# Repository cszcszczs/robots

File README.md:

# Robots (Velocista y Sumo)

##  Esquema de montaje

### *fuente esquemas: https://www.luisllamas.es/arduino-motor-dc-tb6612fng/*
### *fuente codigo base sumo: https://www.youtube.com/watch?v=NjcQ3KwS5uU&t=53s*

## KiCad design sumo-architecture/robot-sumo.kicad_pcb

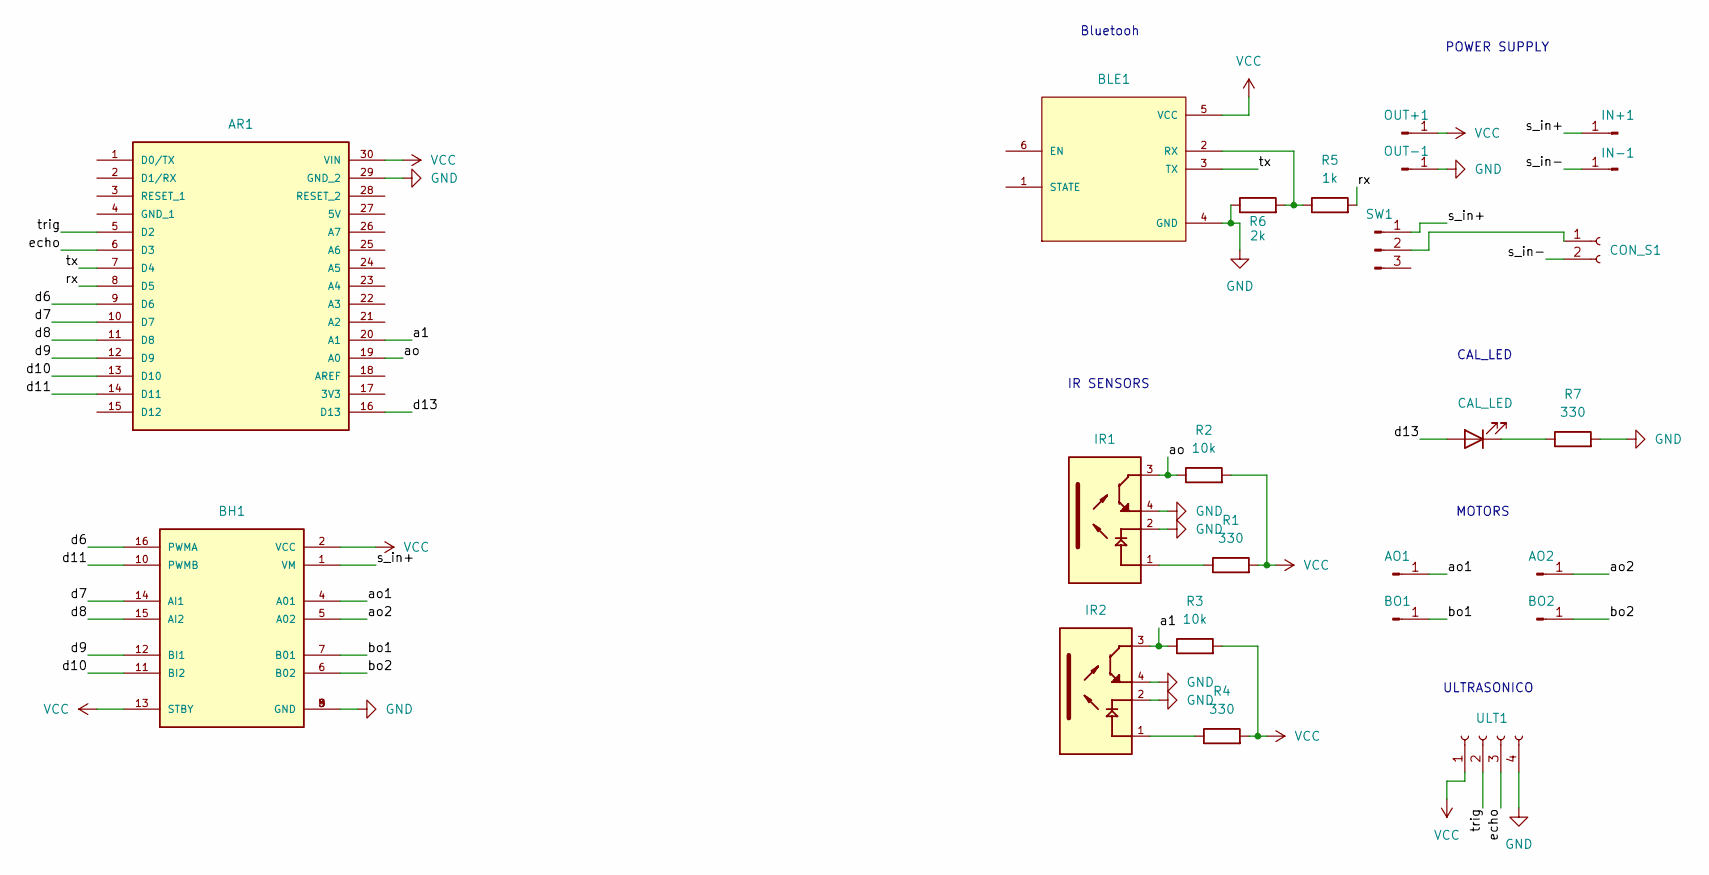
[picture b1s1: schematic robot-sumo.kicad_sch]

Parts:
AO1, AO2: Conn_01x01_Pin; PinHeader_1x01_P1.00mm_Vertical
AR1: A000005; MODULE_A000005; PARTREV 23/03/2020
BH1: ROB-14450; MODULE_ROB-14450; PARTREV 11-13-17
BLE1: ZC142200; MODULE_ZC142200; PARTREV N/A
BO1, BO2: Conn_01x01_Pin; PinHeader_1x01_P1.00mm_Vertical
CAL_LED1: CAL_LED; LED_D5.0mm
CON_S1: Conn_01x02_Socket; AMASS_XT60-M_1x02_P7.20mm_Vertical
IN+1: Conn_01x01_Pin; PinHeader_1x01_P1.00mm_Vertical
IN-1: Conn_01x01_Pin; PinHeader_1x01_P1.00mm_Vertical
IR1, IR2: QRE1113; DIP400W50P180L360H200Q4; PARTREV 5
OUT+1: Conn_01x01_Pin; PinHeader_1x01_P1.00mm_Vertical
OUT-1: Conn_01x01_Pin; PinHeader_1x01_P1.00mm_Vertical
R1, R4, R7: 330; R_Axial_DIN0204_L3.6mm_D1.6mm_P7.62mm_Horizontal
R2, R3: 10k; R_Axial_DIN0204_L3.6mm_D1.6mm_P7.62mm_Horizontal
R5: 1k; R_Axial_DIN0204_L3.6mm_D1.6mm_P7.62mm_Horizontal
R6: 2k; R_Axial_DIN0204_L3.6mm_D1.6mm_P7.62mm_Horizontal
SW1: Conn_01x03_Pin; PinHeader_1x03_P1.00mm_Vertical
ULT1: Conn_01x04_Socket; PinHeader_1x04_P2.00mm_Vertical

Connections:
/a1: AR1.20 (A1), IR2.3, R3.1
/ao: AR1.19 (A0), IR1.3, R2.1
/ao1: AO1.1, BH1.4 (A01)
/ao2: AO2.1, BH1.5 (A02)
/bo1: BH1.7 (B01), BO1.1
/bo2: BH1.6 (B02), BO2.1
/d6: AR1.9 (D6), BH1.16 (PWMA)
/d7: AR1.10 (D7), BH1.14 (AI1)
/d8: AR1.11 (D8), BH1.15 (AI2)
/d9: AR1.12 (D9), BH1.12 (BI1)
/d10: AR1.13 (D10), BH1.11 (BI2)
/d11: AR1.14 (D11), BH1.10 (PWMB)
/d13: AR1.16 (D13), CAL_LED1.2 (A)
/echo: AR1.6 (D3), ULT1.3
/rx: AR1.8 (D5), R5.2
/s_in+: BH1.1 (VM), IN+1.1, SW1.1
/s_in-: CON_S1.2, IN-1.1
/trig: AR1.5 (D2), ULT1.2
/tx: AR1.7 (D4), BLE1.3 (TX)
GND: AR1.29 (GND_2), BH1.3 (GND), BH1.8 (GND), BH1.9 (GND), BLE1.4 (GND), IR1.2, IR1.4, IR2.2, IR2.4, OUT-1.1, R6.1, R7.2, ULT1.4
unnamed: BLE1.2 (RX), R5.1, R6.2
unnamed: CAL_LED1.1 (K), R7.1
unnamed: CON_S1.1, SW1.2
unnamed: IR1.1, R1.1
unnamed: IR2.1, R4.1
VCC: AR1.30 (VIN), BH1.2 (VCC), BH1.13 (STBY), BLE1.5 (VCC), OUT+1.1, R1.2, R2.2, R3.2, R4.2, ULT1.1

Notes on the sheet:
POWER SUPPLY
ULTRASONICO
IR SENSORS
Bluetooh
CAL_LED
MOTORS

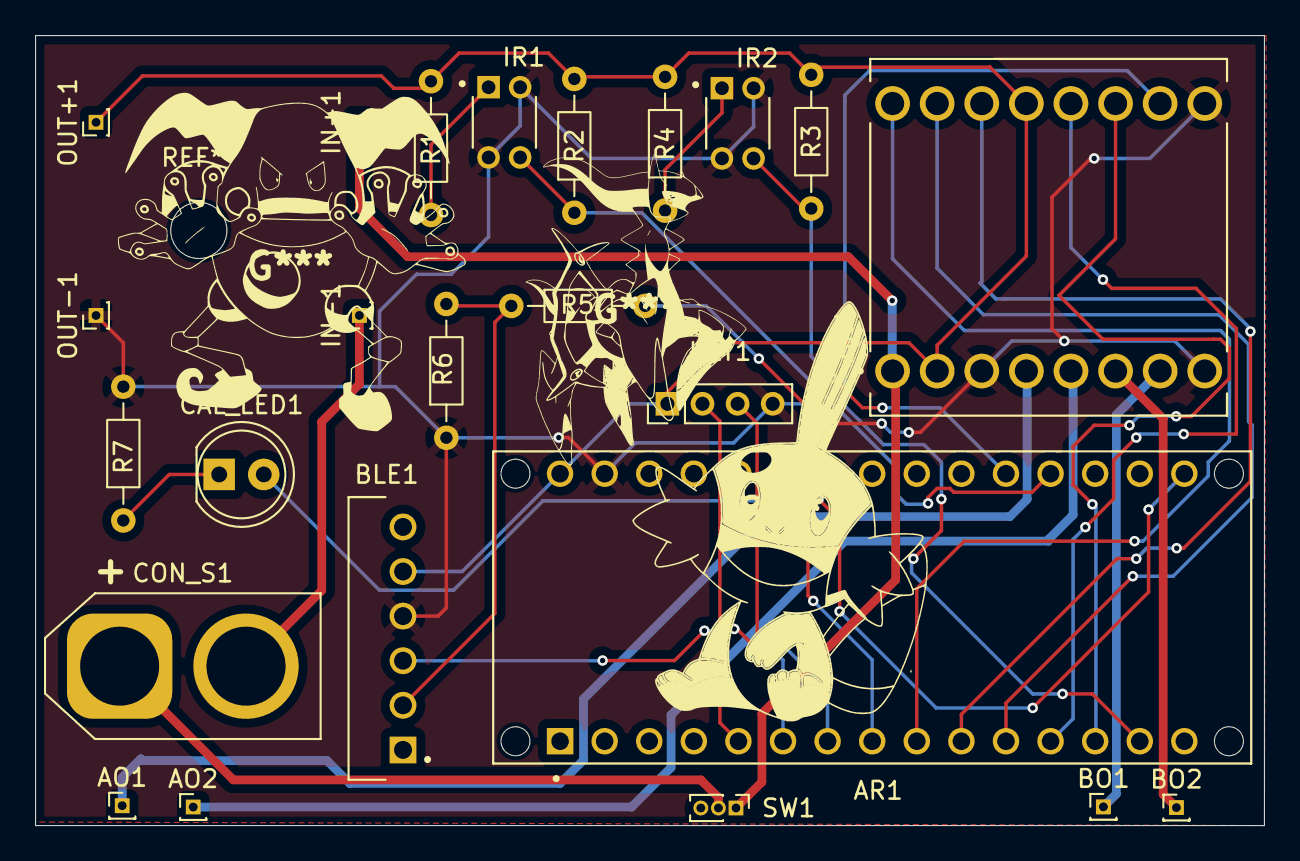
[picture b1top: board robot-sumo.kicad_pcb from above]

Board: 2 copper layers, 70.0 x 45.0 mm, 24 parts (0 on the bottom side), 26 nets.

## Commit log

2025-03-26 agregando el readme
2025-03-26 agregando carpeta assets y modificando el readme
2025-03-26 solucionando errores sintaxis markdown
2025-03-26 agregando comentarios en seguidor_linea.io y agregando source en mardkown
2025-03-26 renombrando carpeta seguidor_linea a velocista
2025-04-09 creando bases del robot sumo
2025-04-11 cambiando puertos del sumo y agregando el codigo de sensores para calibrar y verifivar informacion
2025-04-11 modificando y agregando funciones a los robots
2025-04-11 Create asdasd
2025-04-29 Add proteus project and .gitignore
2025-04-29 Reorganize arduino and h bridge
2025-05-06 Create sumo PCB
2025-05-09 Add leds on the PCB
2025-05-13 Add button on PCB and modify calibrate button circuit
2025-05-24 Final design
2025-11-10 update sumo pcb and its code
2025-11-10 Add sumo PCB folder
2025-11-10 Add sumo PCB backups
2025-11-10 🚀 Sumo code refactor #1
